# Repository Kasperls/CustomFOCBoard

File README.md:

# CustomFOCBoard

A small motor driver board I'm building to run a 27 mm BLDC gimbal motor with field-oriented control. The motor mounts straight onto the board, with its magnet sitting over the encoder chip, so the whole thing ends up as one self-contained motor module you can talk to over CAN or USB.

Designed in KiCad 9, meant to be assembled by JLCPCB.

## What's on it

- STM32G431 microcontroller
- TI DRV8316C three-phase driver with built-in MOSFETs and current sensing
- MT6701 magnetic encoder for the rotor angle
- 3.3 V buck regulator that runs from either the motor supply or USB
- CAN transceiver with two JST-GH connectors, so several boards can be daisy-chained
- USB-C for flashing and serial, plus an SWD header
- Bus voltage and temperature sensing, fault and status LEDs, GND/3V3 test points

The board is 56 × 56 mm, two layers, with all parts on the top. It takes a 4.5–28 V motor supply.

## Some design choices

The DRV8316 is the hardware-configured variant, so everything is set with pins instead of over SPI. It runs in 3x PWM mode, which is what SimpleFOC expects. Current-sense gain is 1.2 V/A, and the slew rate is set to 50 V/µs. That's slower than the max, but cleaner for current measurements, and a small gimbal motor doesn't need more.

The three phase currents go through simple RC filters into the STM32's ADC. The encoder is read over SSI on SPI1.

One quirk: the STM32's BOOT0 pin is shared with CAN RX, which idles high. That means a blank chip boots straight into the USB DFU bootloader, which is handy for the first flash. After that, the option bytes need to be set so it boots from flash.

## Pin map

| Function | STM32 pins |
|---|---|
| PWM (TIM1) | PA8, PA9, PA10 |
| Phase currents (ADC1) | PA0, PA1, PA2 |
| Bus voltage / NTC | PA3 / PB0 |
| Driver nSLEEP / EN / nFAULT | PB2 / PB10 / PB12 |
| Encoder (SPI1) | CS PA15, CLK PB3, DO PB4 |
| CAN (FDCAN1) | RX PB8, TX PB9 |
| USB | PA11, PA12 |
| SWD | PA13, PA14 |
| Status LED | PB6 |

## Files

Open `CustomFOCBoard.kicad_pro` in KiCad 9. The custom symbol and footprint for the DRV8316 live in the project folder, so nothing extra needs to be installed. The JLCPCB BOM is in `CustomFOCBoard_BOM_JLCPCB.csv`. I generate gerbers with the [Fabrication Toolkit](https://github.com/bennymeg/Fabrication-Toolkit) plugin, so they aren't committed here.

## Status

The design is done, but not yet ordered. Next up is a 3D-printed fit check against the motor, then ordering boards and writing firmware with SimpleFOC.

You can also browse the design on [BoardRepo](https://boardrepo.com/kasperls004/customfocboard).

## Use of AI

I have used Claude (Anthropic) to help create this project. It has helped with selecting parts, datasheet cross-checks, design reviews, some schematic and layout edits, and summarizing the project here. I have made the design decisions and reviewed the work. The purpose of the project is to test PCB design with AI support.

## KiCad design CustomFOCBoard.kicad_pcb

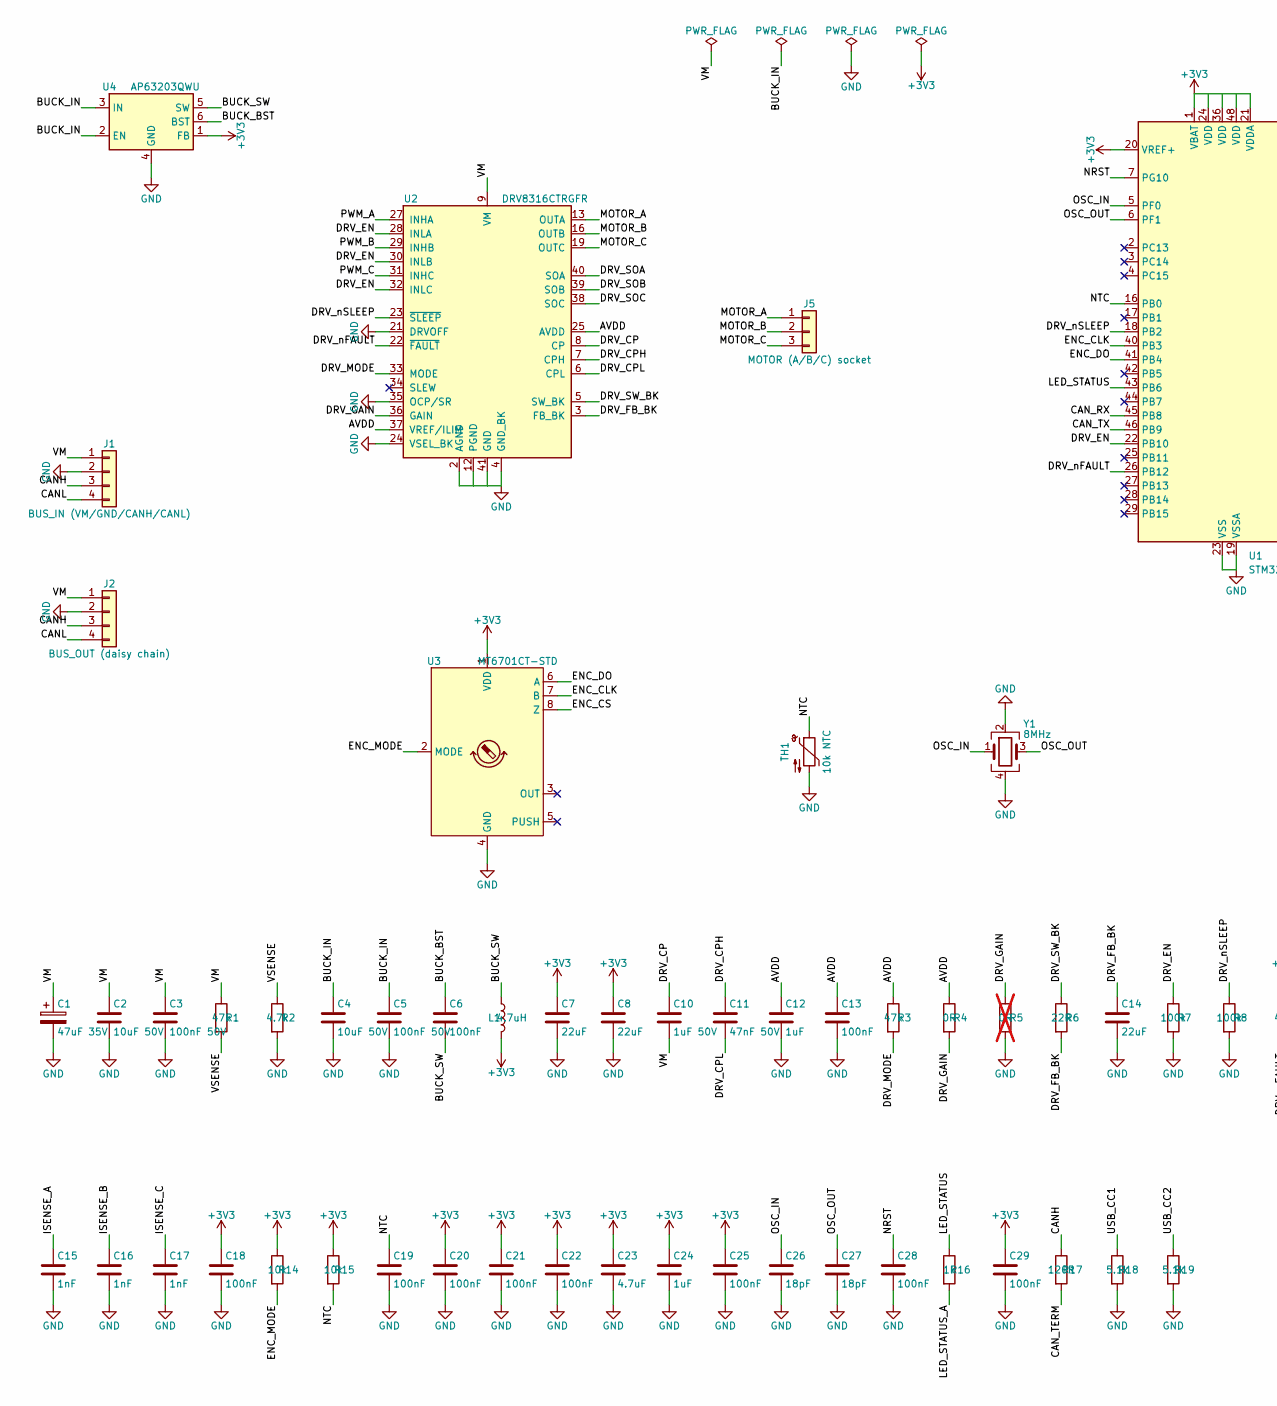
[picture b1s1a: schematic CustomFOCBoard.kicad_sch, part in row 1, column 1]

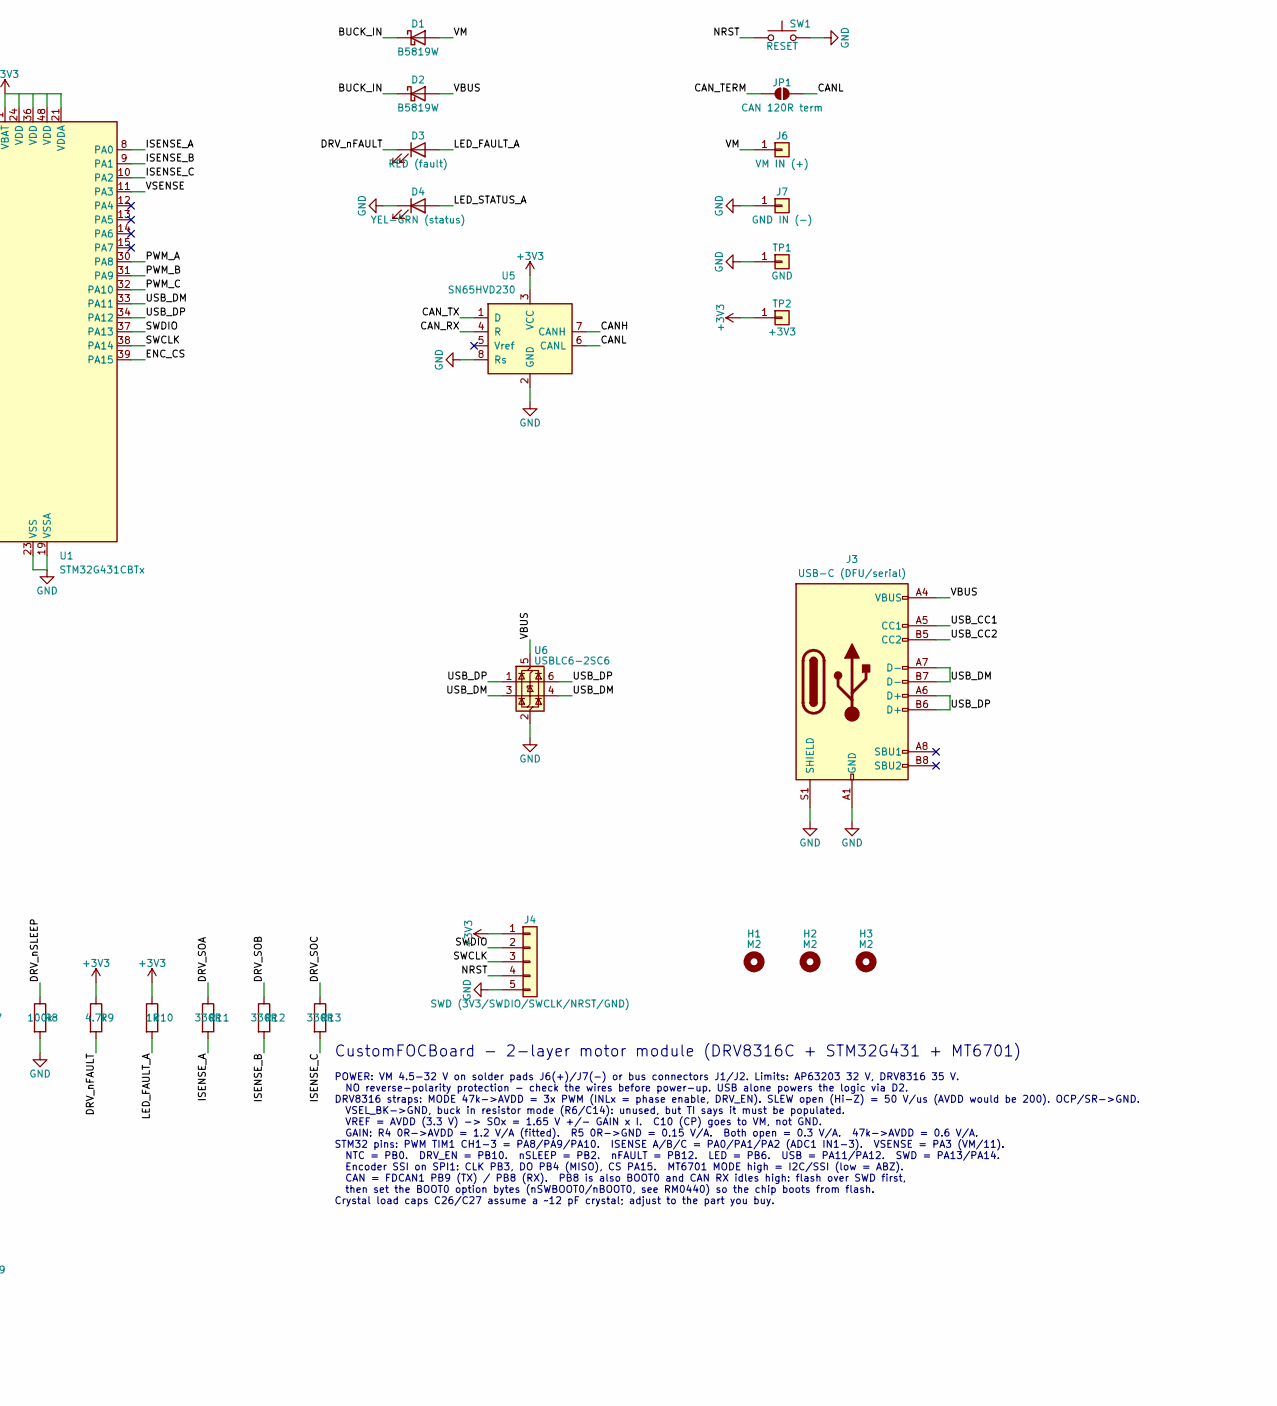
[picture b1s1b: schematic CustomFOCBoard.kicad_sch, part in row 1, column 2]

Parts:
C1: 47uF 35V; CP_Elec_6.3x5.2; LCSC C110229
C2: 10uF 50V; C_1210_3225Metric; LCSC C138687
C3, C5: 100nF 50V; C_0603_1608Metric; LCSC C14663
C4: 10uF 50V; C_1206_3216Metric; LCSC C13585
C6, C13, C18, C19, C20, C21, C22, C25, C28, C29: 100nF; C_0603_1608Metric; LCSC C14663
C7, C8, C14: 22uF; C_0805_2012Metric; LCSC C45783
C10: 1uF 50V; C_0603_1608Metric; LCSC C15849
C11: 47nF 50V; C_0603_1608Metric; LCSC C1622
C12, C24: 1uF; C_0603_1608Metric; LCSC C15849
C15, C16, C17: 1nF; C_0603_1608Metric; LCSC C1588
C23: 4.7uF; C_0603_1608Metric; LCSC C19666
C26, C27: 18pF; C_0603_1608Metric; LCSC C1647
D1, D2: B5819W; D_SOD-123; LCSC C8598
D3: RED (fault); LED_0603_1608Metric; LCSC C2286
D4: YEL-GRN (status); LED_0603_1608Metric; LCSC C2289
H1, H2, H3: M2; MountingHole_2.2mm_M2
J1: BUS_IN (VM/GND/CANH/CANL); JST_GH_SM04B-GHS-TB_1x04-1MP_P1.25mm_Horizontal; LCSC C189895
J2: BUS_OUT (daisy chain); JST_GH_SM04B-GHS-TB_1x04-1MP_P1.25mm_Horizontal; LCSC C189895
J3: USB-C (DFU/serial); USB_C_Receptacle_HRO_TYPE-C-31-M-12; LCSC C165948
J4: SWD (3V3/SWDIO/SWCLK/NRST/GND); PinHeader_1x05_P1.27mm_Vertical
J5: MOTOR (A/B/C) socket; PinSocket_1x03_P2.54mm_Vertical
J6: VM IN (+); SolderWire-0.5sqmm_1x01_D0.9mm_OD2.1mm
J7: GND IN (-); SolderWire-0.5sqmm_1x01_D0.9mm_OD2.1mm
JP1: CAN 120R term; SolderJumper-2_P1.3mm_Open_RoundedPad1.0x1.5mm
L1: 4.7uH; L_Bourns-SRN4018; LCSC C167806
R1, R3: 47k; R_0603_1608Metric; LCSC C25819
R2, R9: 4.7k; R_0603_1608Metric; LCSC C23162
R4: 0R; R_0603_1608Metric; LCSC C21189
R5: 0R; R_0603_1608Metric; LCSC C21189; not fitted
R6: 22R; R_0603_1608Metric; LCSC C23345
R7, R8: 100k; R_0603_1608Metric; LCSC C25803
R10, R16: 1k; R_0603_1608Metric; LCSC C21190
R11, R12, R13: 330R; R_0603_1608Metric; LCSC C23138
R14, R15: 10k; R_0603_1608Metric; LCSC C25804
R17: 120R; R_0603_1608Metric; LCSC C22787
R18, R19: 5.1k; R_0603_1608Metric; LCSC C23186
SW1: RESET; SW_Push_1P1T_XKB_TS-1187A; LCSC C318884
TH1: 10k NTC; R_0603_1608Metric; LCSC C13564
TP1: GND; TestPoint_THTPad_D2.0mm_Drill1.0mm
TP2: +3V3; TestPoint_Pad_D1.5mm
U1: STM32G431CBTx; LQFP-48_7x7mm_P0.5mm; LCSC C529355
U2: DRV8316CTRGFR; Texas_RGF0040E_VQFN-40-1EP_7x5mm_P0.5mm_EP5.7x3.7mm_Thermal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; LCSC C6602057
U3: MT6701CT-STD; SO-8_3.9x4.9mm_P1.27mm; LCSC C5451785
U4: AP63203QWU; TSOT-23-6; LCSC C5248536
U5: SN65HVD230; SOIC-8_3.9x4.9mm_P1.27mm; LCSC C12084
U6: USBLC6-2SC6; SOT-23-6; LCSC C7519
Y1: 8MHz; Crystal_SMD_3225-4Pin_3.2x2.5mm; LCSC C2682775

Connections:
+3V3: C7.1, C8.1, C18.1, C20.1, C21.1, C22.1, C23.1, C24.1, C25.1, C29.1, J4.1, L1.2, R9.1, R10.1, R14.1, R15.1, TP2.1, U1.1 (VBAT), U1.20 (VREF+), U1.21 (VDDA), U1.24 (VDD), U1.36 (VDD), U1.48 (VDD), U3.1 (VDD), U4.1 (FB), U5.3 (VCC)
/AVDD: C12.1, C13.1, R3.1, R4.1, U2.25 (AVDD), U2.37 (VREF/ILIM)
/BUCK_BST: C6.1, U4.6 (BST)
/BUCK_IN: C4.1, C5.1, D1.1 (K), D2.1 (K), U4.2 (EN), U4.3 (IN)
/BUCK_SW: C6.2, L1.1, U4.5 (SW)
/CANH: J1.3, J2.3, R17.1, U5.7 (CANH)
/CANL: J1.4, J2.4, JP1.2 (B), U5.6 (CANL)
/CAN_RX: U1.45 (PB8), U5.4 (R)
/CAN_TERM: JP1.1 (A), R17.2
/CAN_TX: U1.46 (PB9), U5.1 (D)
/DRV_CP: C10.1, U2.8 (CP)
/DRV_CPH: C11.1, U2.7 (CPH)
/DRV_CPL: C11.2, U2.6 (CPL)
/DRV_EN: R7.1, U1.22 (PB10), U2.28 (INLA), U2.30 (INLB), U2.32 (INLC)
/DRV_FB_BK: C14.1, R6.2, U2.3 (FB_BK)
/DRV_GAIN: R4.2, R5.1, U2.36 (GAIN)
/DRV_MODE: R3.2, U2.33 (MODE)
/DRV_SOA: R11.1, U2.40 (SOA)
/DRV_SOB: R12.1, U2.39 (SOB)
/DRV_SOC: R13.1, U2.38 (SOC)
/DRV_SW_BK: R6.1, U2.5 (SW_BK)
/DRV_nFAULT: D3.1 (K), R9.2, U1.26 (PB12), U2.22 (~FAULT)
/DRV_nSLEEP: R8.1, U1.18 (PB2), U2.23 (~SLEEP)
/ENC_CLK: U1.40 (PB3), U3.7 (B)
/ENC_CS: U1.39 (PA15), U3.8 (Z)
/ENC_DO: U1.41 (PB4), U3.6 (A)
/ENC_MODE: R14.2, U3.2 (MODE)
/ISENSE_A: C15.1, R11.2, U1.8 (PA0)
/ISENSE_B: C16.1, R12.2, U1.9 (PA1)
/ISENSE_C: C17.1, R13.2, U1.10 (PA2)
/LED_FAULT_A: D3.2 (A), R10.2
/LED_STATUS: R16.1, U1.43 (PB6)
/LED_STATUS_A: D4.2 (A), R16.2
/MOTOR_A: J5.1, U2.13 (OUTA), U2.14 (OUTA)
/MOTOR_B: J5.2, U2.16 (OUTB), U2.17 (OUTB)
/MOTOR_C: J5.3, U2.19 (OUTC), U2.20 (OUTC)
/NRST: C28.1, J4.4, SW1.1, U1.7 (PG10)
/NTC: C19.1, R15.2, TH1.1, U1.16 (PB0)
/OSC_IN: C26.1, U1.5 (PF0), Y1.1
/OSC_OUT: C27.1, U1.6 (PF1), Y1.3
/PWM_A: U1.30 (PA8), U2.27 (INHA)
/PWM_B: U1.31 (PA9), U2.29 (INHB)
/PWM_C: U1.32 (PA10), U2.31 (INHC)
/SWCLK: J4.3, U1.38 (PA14)
/SWDIO: J4.2, U1.37 (PA13)
/USB_CC1: J3.A5 (CC1), R18.1
/USB_CC2: J3.B5 (CC2), R19.1
/USB_DM: J3.A7 (D-), J3.B7 (D-), U1.33 (PA11), U6.3 (I/O2), U6.4 (I/O2)
/USB_DP: J3.A6 (D+), J3.B6 (D+), U1.34 (PA12), U6.1 (I/O1), U6.6 (I/O1)
/VBUS: D2.2 (A), J3.A4 (VBUS), J3.A9 (VBUS), J3.B4 (VBUS), J3.B9 (VBUS), U6.5 (VBUS)
/VM: C1.1, C2.1, C3.1, C10.2, D1.2 (A), J1.1, J2.1, J6.1, R1.1, U2.9 (VM), U2.10 (VM), U2.11 (VM)
/VSENSE: R1.2, R2.1, U1.11 (PA3)
GND: C1.2, C2.2, C3.2, C4.2, C5.2, C7.2, C8.2, C12.2, C13.2, C14.2, C15.2, C16.2, C17.2, C18.2, C19.2, C20.2, C21.2, C22.2, C23.2, C24.2, C25.2, C26.2, C27.2, C28.2, C29.2, D4.1 (K), J1.2, J2.2, J3.A1 (GND), J3.A12 (GND), J3.B1 (GND), J3.B12 (GND), J3.S1 (SHIELD), J4.5, J7.1, R2.2, R5.2, R7.2, R8.2, R18.2, R19.2, SW1.2, TH1.2, TP1.1, U1.19 (VSSA), U1.23 (VSS), U1.35 (VSS), U1.47 (VSS), U2.2 (AGND), U2.4 (GND_BK), U2.12 (PGND), U2.15 (PGND), U2.18 (PGND), U2.21 (DRVOFF), U2.24 (VSEL_BK), U2.26 (AGND), U2.35 (OCP/SR), U2.41 (GND), U3.4 (GND), U4.4 (GND), U5.2 (GND), U5.8 (Rs), U6.2 (GND), Y1.2, Y1.4

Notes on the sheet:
CustomFOCBoard - 2-layer motor module (DRV8316C + STM32G431 + MT6701)
POWER: VM 4.5-32 V on solder pads J6(+)/J7(-) or bus connectors J1/J2. Limits: AP63203 32 V, DRV8316 35 V. NO reverse-polarity protection - check the wires before power-up. USB alone powers the logic via D2. DRV8316 straps: MODE 47k->AVDD = 3x PWM (INLx = phase enable, DRV_EN). SLEW open (Hi-Z) = 5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

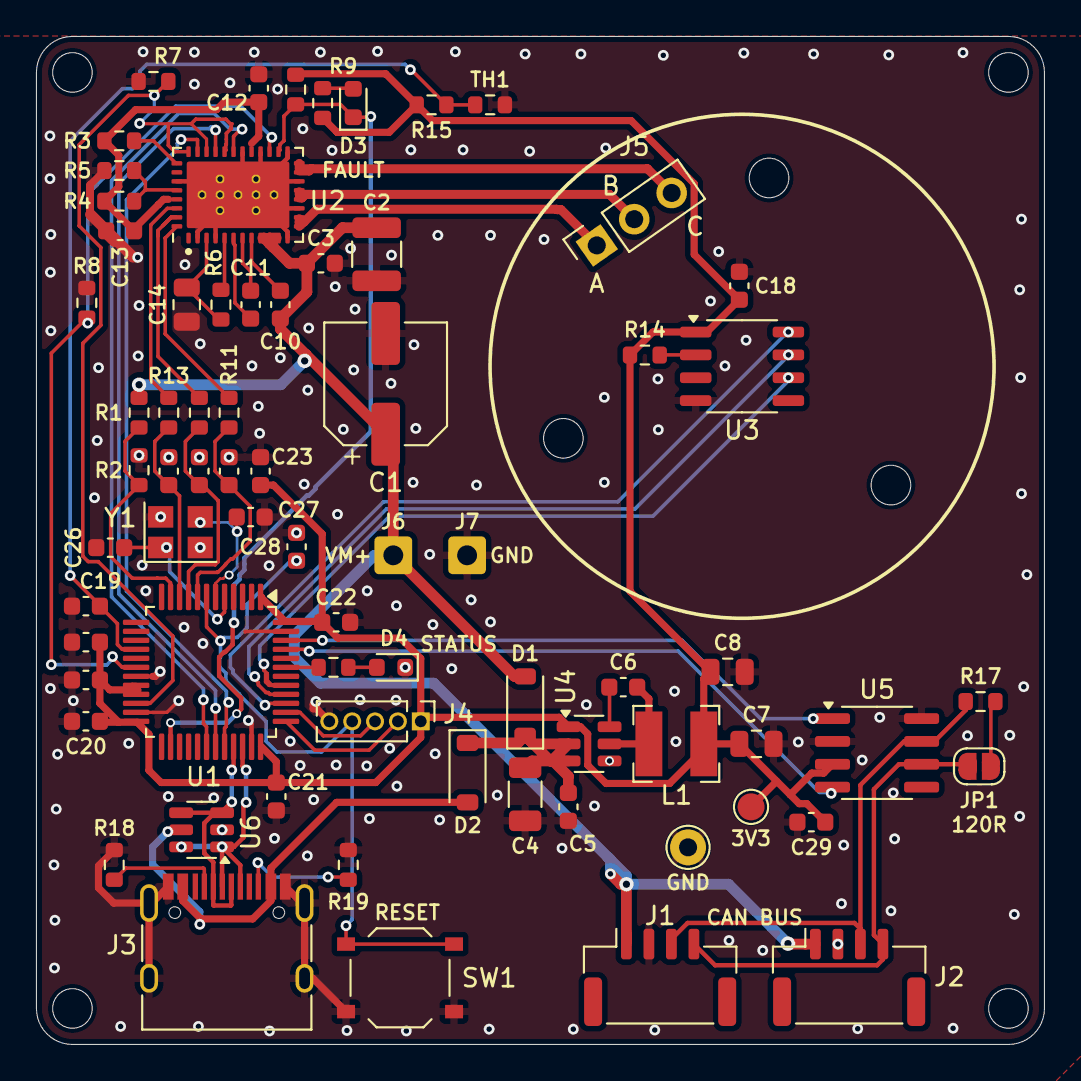
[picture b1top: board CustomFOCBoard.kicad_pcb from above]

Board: 2 copper layers, 56.0 x 56.0 mm, 78 parts (0 on the bottom side), 53 nets.

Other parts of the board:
H4, H5, H6, H7: M2; MountingHole_2.2mm_M2

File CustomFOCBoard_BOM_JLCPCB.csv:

Comment,Designator,Footprint,LCSC,Qty,Part
47uF 35V,C1,CP_Elec_6.3x5.2,C110229,1,CS1V470M-CRE54 47uF 35V
10uF 50V,C2,C_1210_3225Metric,C138687,1,Samsung CL32B106KBJNNNE 10uF 50V 1210
100nF 50V,"C3,C5,C6,C13,C18,C19,C20,C21,C22,C25,C28,C29",C_0603_1608Metric,C14663,12,100nF 50V X7R 0603
10uF 50V,C4,C_1206_3216Metric,C13585,1,Samsung CL31A106KBHNNNE 10uF 50V 1206
22uF,"C7,C8,C14",C_0805_2012Metric,C45783,3,22uF 25V X5R 0805
1uF 50V,"C10,C12,C24",C_0603_1608Metric,C15849,3,1uF 50V X5R 0603
47nF 50V,C11,C_0603_1608Metric,C1622,1,47nF 50V X7R 0603
1nF,"C15,C16,C17",C_0603_1608Metric,C1588,3,1nF 50V X7R 0603
4.7uF,C23,C_0603_1608Metric,C19666,1,4.7uF 25V X5R 0603
18pF,"C26,C27",C_0603_1608Metric,C1647,2,18pF 50V C0G 0603
B5819W,"D1,D2",D_SOD-123,C8598,2,B5819W SL
RED (fault),D3,LED_0603_1608Metric,C2286,1,KENTO KT-0603R red
YEL-GRN (status),D4,LED_0603_1608Metric,C2289,1,KENTO KT-0603YG yellow-green
SM04B-GHS-TB,"J1,J2",JST_GH_SM04B-GHS-TB_1x04-1MP_P1.25mm_Horizontal,C189895,2,JST SM04B-GHS-TB
USB-C (DFU/serial),J3,USB_C_Receptacle_HRO_TYPE-C-31-M-12,C165948,1,HRO TYPE-C-31-M-12
4.7uH,L1,L_Bourns-SRN4018,C167806,1,cjiang FNR4018S4R7MT 4.7uH
47k,"R1,R3",R_0603_1608Metric,C25819,2,47k 1% 0603
4.7k,"R2,R9",R_0603_1608Metric,C23162,2,4.7k 1% 0603
0R,R4,R_0603_1608Metric,C21189,1,0R 0603
22R,R6,R_0603_1608Metric,C23345,1,22R 1% 0603
100k,"R7,R8",R_0603_1608Metric,C25803,2,100k 1% 0603
1k,"R10,R16",R_0603_1608Metric,C21190,2,1k 1% 0603
330R,"R11,R12,R13",R_0603_1608Metric,C23138,3,330R 1% 0603
10k,"R14,R15",R_0603_1608Metric,C25804,2,10k 1% 0603
120R,R17,R_0603_1608Metric,C22787,1,120R 1% 0603
5.1k,"R18,R19",R_0603_1608Metric,C23186,2,5.1k 1% 0603
RESET,SW1,SW_Push_1P1T_XKB_TS-1187A,C318884,1,XKB TS-1187A-B-A-B
10k NTC,TH1,R_0603_1608Metric,C13564,1,Murata NCP18XH103F03RB
STM32G431CBTx,U1,LQFP-48_7x7mm_P0.5mm,C529355,1,STM32G431CBT6
DRV8316CTRGFR,U2,Texas_RGF0040E_VQFN-40-1EP_7x5mm_P0.5mm_EP5.7x3.7mm_ThermalVias,C6602057,1,DRV8316CTRGFR
MT6701CT-STD,U3,SO-8_3.9x4.9mm_P1.27mm,C5451785,1,MT6701CT-STD
AP63203QWU,U4,TSOT-23-6,C5248536,1,AP63203QWU-7
SN65HVD230,U5,SOIC-8_3.9x4.9mm_P1.27mm,C12084,1,SN65HVD230DR
USBLC6-2SC6,U6,SOT-23-6,C7519,1,USBLC6-2SC6
8MHz,Y1,Crystal_SMD_3225-4Pin_3.2x2.5mm,C2682775,1,YXC X32258MOB4SI 8MHz CL12pF
